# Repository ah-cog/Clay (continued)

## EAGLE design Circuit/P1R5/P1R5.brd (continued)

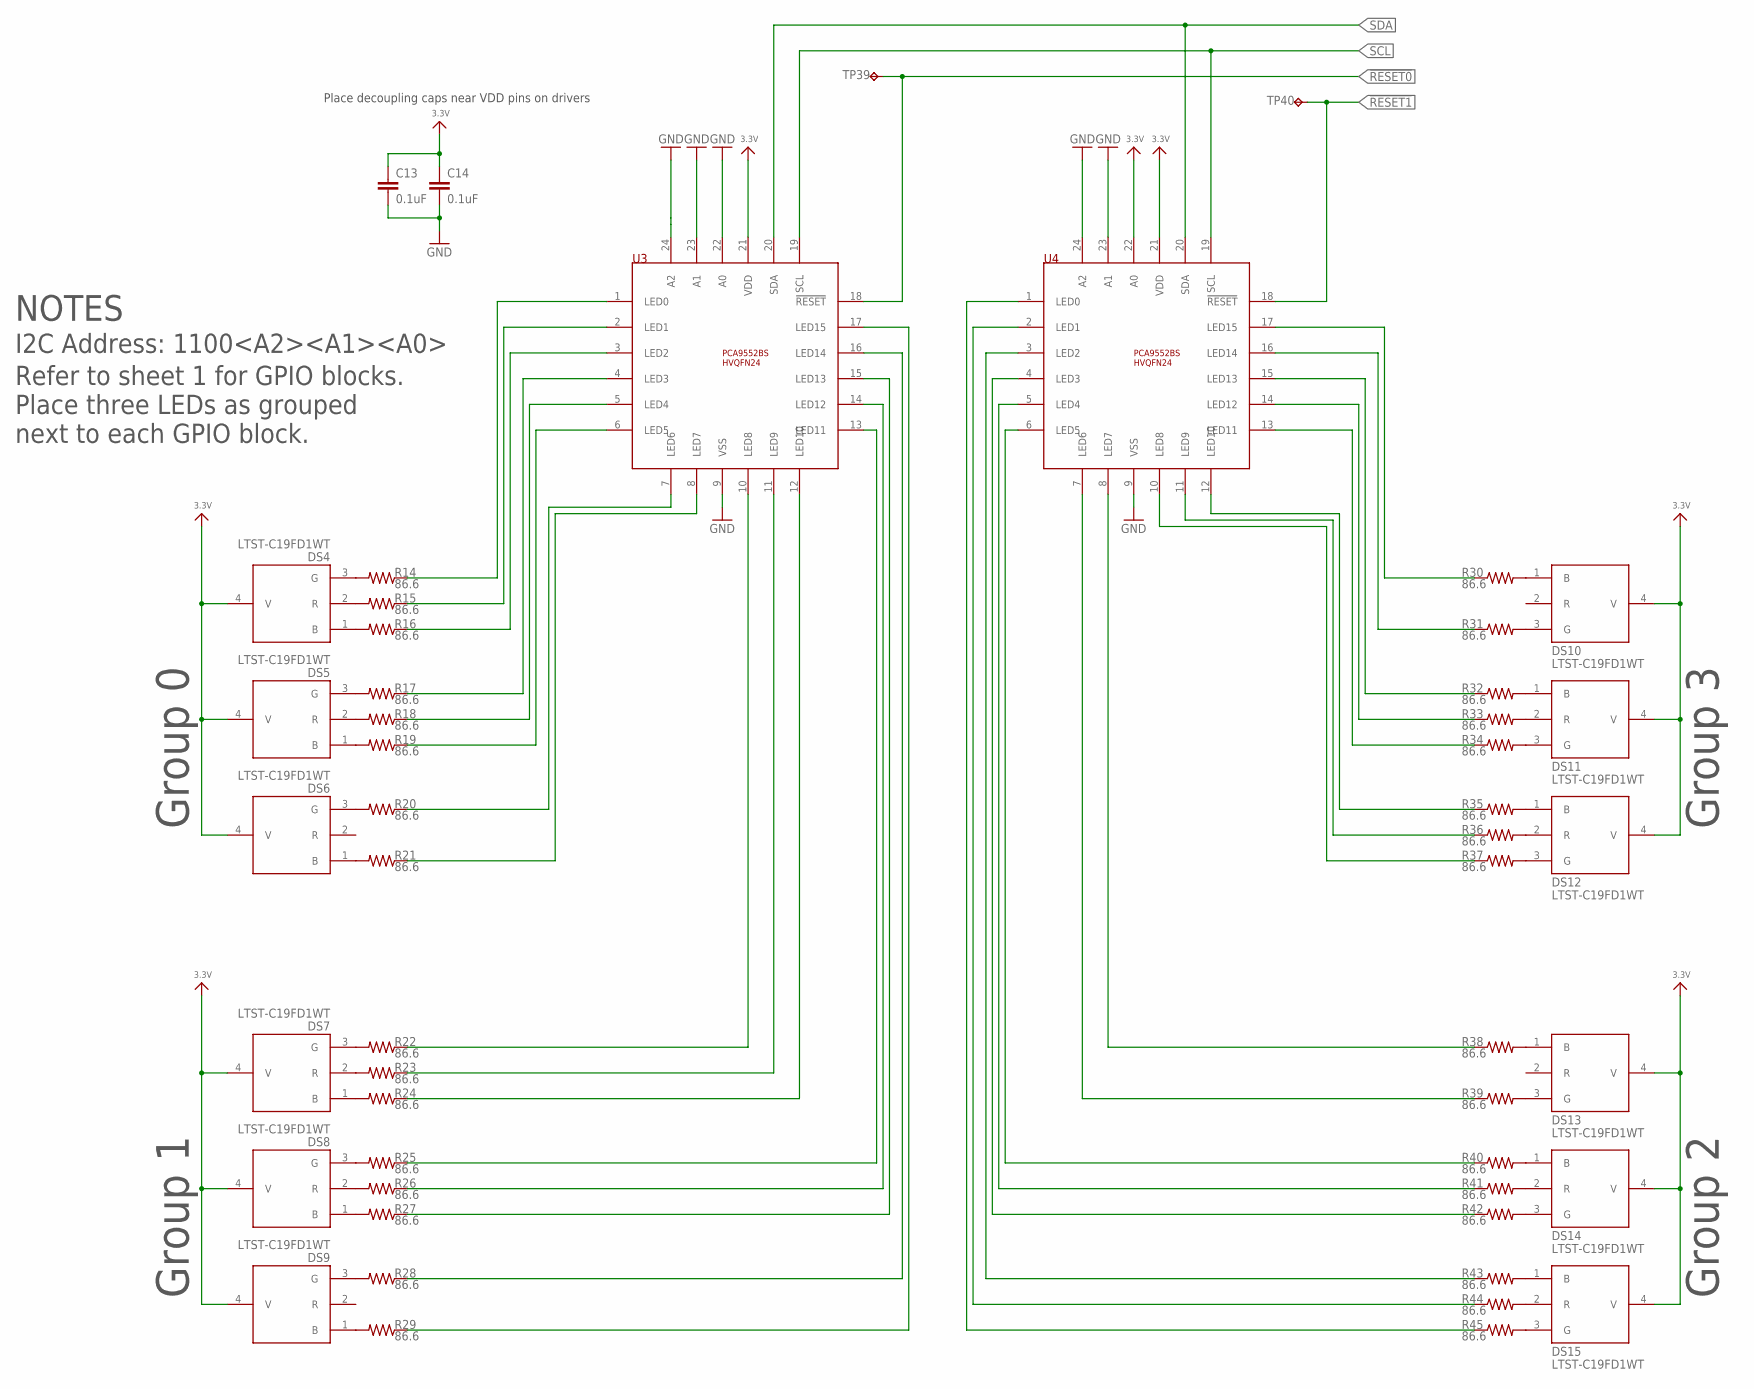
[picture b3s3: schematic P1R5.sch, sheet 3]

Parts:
C13, C14: 0.1uF; 0402-CAP; PARTNO C1005X7R1C104K050BC
DS4, DS5, DS6, DS7, DS8, DS9, DS10, DS11, DS12, DS13, DS14, DS15: LTST-C19FD1WT; PARTNO LTST-C19FD1WT
R14, R15, R16, R17, R18, R19, R20, R21, R22, R23, R24, R25, R26, R27, R28, R29, R30, R31, R32, R33, R34, R35, R36, R37, R38, R39, R40, R41, R42, R43, R44, R45: 86.6; _0402; PARTNO 5-1879213-0
TP39, TP40: TPTP08R; TP08R; PARTNO TEST POINT
U3, U4: PCA9552BS; HVQFN24; PARTNO PCA9552BS

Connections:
3.3V: C13.1, C14.1, DS4.4 (V), DS5.4 (V), DS6.4 (V), DS7.4 (V), DS8.4 (V), DS9.4 (V), DS10.4 (V), DS11.4 (V), DS12.4 (V), DS13.4 (V), DS14.4 (V), DS15.4 (V), U3.21 (VDD), U4.21 (VDD), U4.22 (A0); also elsewhere on the board
!RESET0: TP39.TP, U3.18 (!RESET); also elsewhere on the board
!RESET1: TP40.TP, U4.18 (!RESET); also elsewhere on the board
GND: C13.2, C14.2, U3.9 (VSS), U3.22 (A0), U3.23 (A1), U3.24 (A2), U4.9 (VSS), U4.23 (A1), U4.24 (A2); also elsewhere on the board
unnamed: DS8.2 (R), R26.2
unnamed: DS7.2 (R), R23.2
unnamed: DS7.1 (B), R24.2
unnamed: DS7.3 (G), R22.2
unnamed: DS8.1 (B), R27.2
unnamed: DS8.3 (G), R25.2
unnamed: DS10.3 (G), R31.2
unnamed: DS10.1 (B), R30.2
unnamed: DS9.1 (B), R29.2
unnamed: DS9.3 (G), R28.2
unnamed: R14.1, U3.1 (LED0)
unnamed: DS5.2 (R), R18.2
unnamed: R15.1, U3.2 (LED1)
unnamed: R16.1, U3.3 (LED2)
unnamed: DS14.1 (B), R40.2
unnamed: DS4.2 (R), R15.2
unnamed: DS11.2 (R), R33.2
unnamed: DS4.1 (B), R16.2
unnamed: DS4.3 (G), R14.2
unnamed: DS5.1 (B), R19.2
unnamed: DS5.3 (G), R17.2
unnamed: DS15.3 (G), R45.2
unnamed: DS12.1 (B), R35.2
unnamed: DS13.3 (G), R39.2
unnamed: R17.1, U3.4 (LED3)
unnamed: DS11.3 (G), R34.2
unnamed: DS14.3 (G), R42.2
unnamed: DS11.1 (B), R32.2
unnamed: DS12.3 (G), R37.2
unnamed: DS6.1 (B), R21.2
unnamed: DS6.3 (G), R20.2
unnamed: DS14.2 (R), R41.2
unnamed: DS13.1 (B), R38.2
unnamed: R18.1, U3.5 (LED4)
unnamed: DS15.1 (B), R43.2
unnamed: R19.1, U3.6 (LED5)
unnamed: R20.1, U3.7 (LED6)
unnamed: R21.1, U3.8 (LED7)
unnamed: R22.1, U3.10 (LED8)
unnamed: R23.1, U3.11 (LED9)
unnamed: R24.1, U3.12 (LED10)
unnamed: R25.1, U3.13 (LED11)
unnamed: R26.1, U3.14 (LED12)
unnamed: R27.1, U3.15 (LED13)
unnamed: R28.1, U3.16 (LED14)
unnamed: R29.1, U3.17 (LED15)
unnamed: DS12.2 (R), R36.2
unnamed: DS15.2 (R), R44.2
unnamed: R30.1, U4.17 (LED15)
unnamed: R31.1, U4.16 (LED14)
unnamed: R32.1, U4.15 (LED13)
unnamed: R33.1, U4.14 (LED12)
unnamed: R34.1, U4.13 (LED11)
unnamed: R35.1, U4.12 (LED10)
unnamed: R36.1, U4.11 (LED9)
unnamed: R37.1, U4.10 (LED8)
unnamed: R38.1, U4.8 (LED7)
unnamed: R39.1, U4.7 (LED6)
unnamed: R40.1, U4.6 (LED5)
unnamed: R41.1, U4.5 (LED4)
unnamed: R42.1, U4.4 (LED3)
unnamed: R43.1, U4.3 (LED2)
unnamed: R44.1, U4.2 (LED1)
unnamed: R45.1, U4.1 (LED0)
SCL: U3.19 (SCL), U4.19 (SCL); also elsewhere on the board
SDA: U3.20 (SDA), U4.20 (SDA); also elsewhere on the board

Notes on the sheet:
I2C Address: 1100<A2><A1><A0>
Place decoupling caps near VDD pins on drivers
Refer to sheet 1 for GPIO blocks. Place three LEDs as grouped next to each GPIO block.
NOTES
Group 0
Group 1
Group 2
Group 3

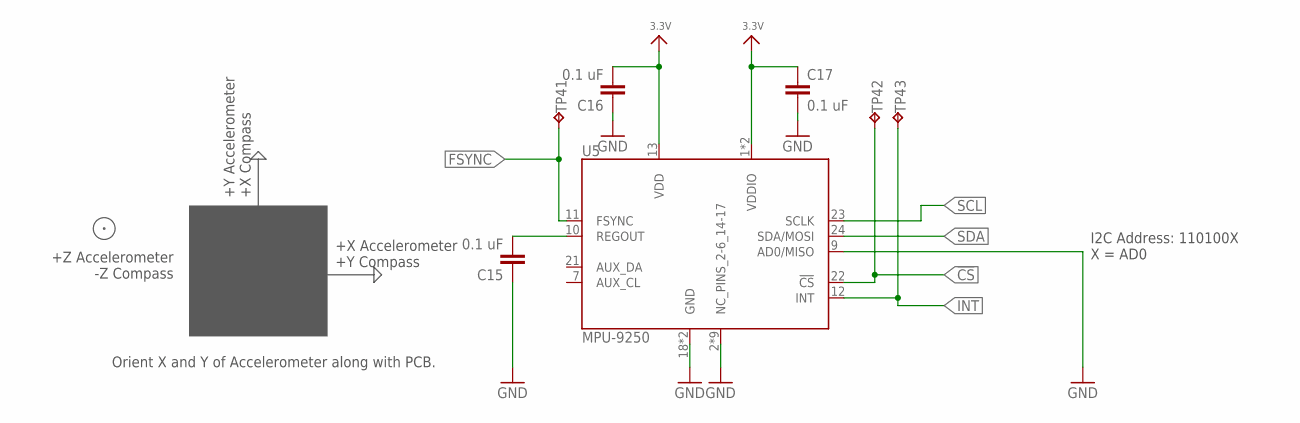
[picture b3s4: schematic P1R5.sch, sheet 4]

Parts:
C15, C16, C17: 0.1 uF; 0402-CAP; PARTNO C1005X7R1C104K050BC
TP41, TP42, TP43: TPTP08R; TP08R; PARTNO TEST POINT
U5: MPU-9250; QFN-24/3MM; PARTNO MPU-9250

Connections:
3.3V: C16.2, C17.1, U5.1 (VDDIO), U5.8 (VDDIO), U5.13 (VDD); also elsewhere on the board
!CS: TP42.TP, U5.22 (!CS); also elsewhere on the board
FSYNC: TP41.TP, U5.11 (FSYNC); also elsewhere on the board
GND: C15.1, C16.1, C17.2, U5.2 (NC_PINS_2-6_14-17), U5.3 (NC_PINS_2-6_14-17), U5.4 (NC_PINS_2-6_14-17), U5.5 (NC_PINS_2-6_14-17), U5.6 (NC_PINS_2-6_14-17), U5.9 (AD0/MISO), U5.14 (NC_PINS_2-6_14-17), U5.15 (NC_PINS_2-6_14-17), U5.16 (NC_PINS_2-6_14-17), U5.17 (NC_PINS_2-6_14-17), U5.18 (GND), U5.20 (GND); also elsewhere on the board
INT: TP43.TP, U5.12 (INT); also elsewhere on the board
unnamed: C15.2, U5.10 (REGOUT)
SCL: U5.23 (SCLK); also elsewhere on the board
SDA: U5.24 (SDA/MOSI); also elsewhere on the board

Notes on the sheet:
Orient X and Y of Accelerometer along with PCB.
+Y Accelerometer +X Compass
+X Accelerometer +Y Compass
I2C Address: 110100X X = AD0
+Z Accelerometer -Z Compass

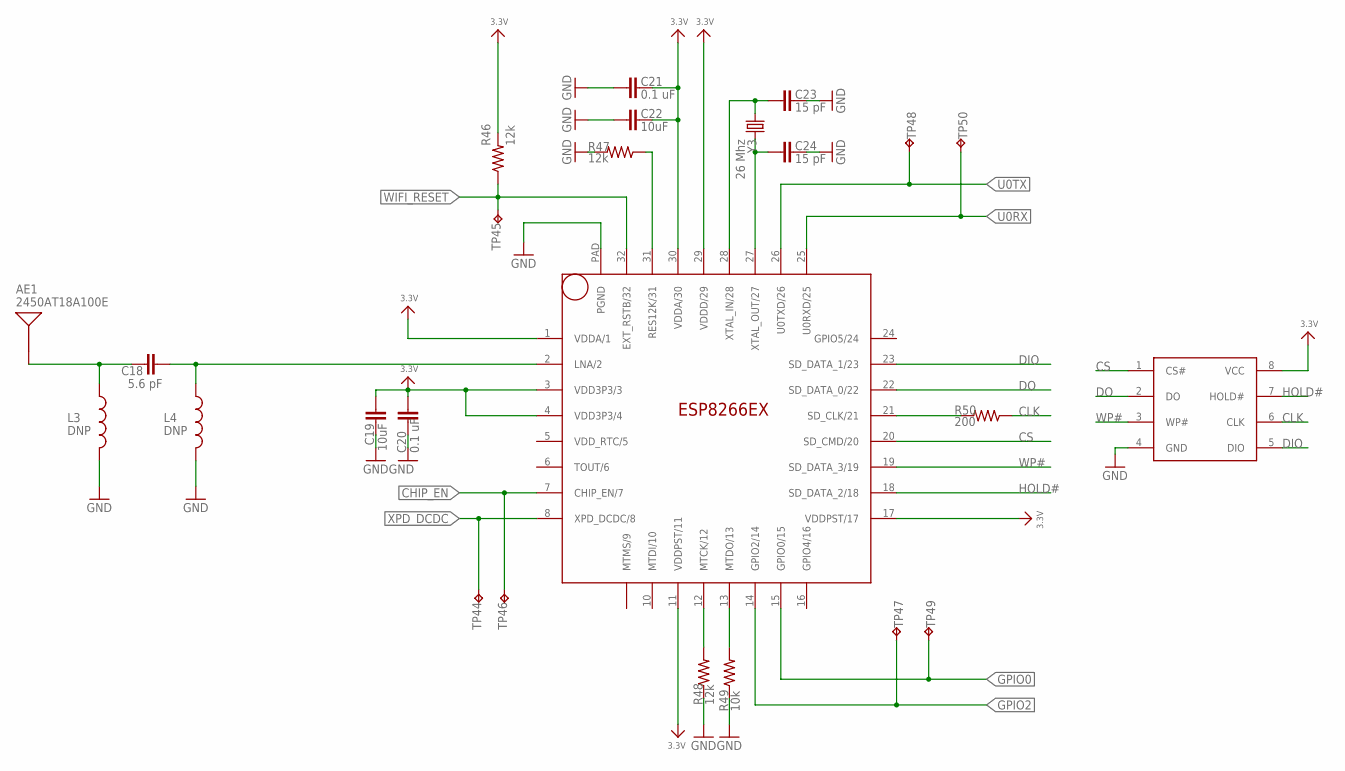
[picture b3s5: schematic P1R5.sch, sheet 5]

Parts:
AE1: 2450AT18A100E; ANTENNA-CHIP2; PARTNO 2450AT18A100E
C18: 5.6 pF; 0402-CAP; PARTNO GRM1555C1H5R6CA01D
C19, C22: 10uF; 0603-CAP; PARTNO C1608X7S0J106M080AC
C20, C21: 0.1 uF; 0402-CAP; PARTNO C1005X7R1C104K050BC
C23, C24: 15 pF; 0402-CAP; PARTNO C1005C0G1H150J050BA
L3, L4: DNP; 0603; PARTNO DNP
R46, R47, R48: 12k; _0402; PARTNO CRCW040212K0FKED
R49: 10k; _0402; PARTNO CRCW040210K0FKED
R50: 200; _0402; PARTNO CRCW0402200RFKED
TP44, TP45, TP46, TP47, TP48, TP49, TP50: TPTP08R; TP08R; PARTNO TEST POINT
U6: ESP8266EX; QFN32; PARTNO ESP8266EX
U7: 25Q40; SOP8; PARTNO 25Q40
Y3: 26 Mhz; CRYSTAL-SMD-5X3; PARTNO 7M-26.000MAAJ-T

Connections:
3.3V: C19.1, C20.2, C21.1, C22.1, R46.2, U6.1 (VDDA/1), U6.3 (VDD3P3/3), U6.4 (VDD3P3/4), U6.11 (VDDPST/11), U6.17 (VDDPST/17), U6.29 (VDDD/29), U6.30 (VDDA/30), U7.8 (VCC); also elsewhere on the board
CHIP_EN: TP46.TP, U6.7 (CHIP_EN/7); also elsewhere on the board
CLK: R50.1, U7.6 (CLK)
CS: U6.20 (SD_CMD/20), U7.1 (CS#)
DIO: U6.23 (SD_DATA_1/23), U7.5 (DIO)
DO: U6.22 (SD_DATA_0/22), U7.2 (DO)
GND: C19.2, C20.1, C21.2, C22.2, C23.2, C24.2, L3.2, L4.2, R47.2, R48.1, R49.1, U6.PAD (PGND), U7.4 (GND); also elsewhere on the board
GPIO0: TP49.TP, U6.15 (GPIO0/15); also elsewhere on the board
GPIO2: TP47.TP, U6.14 (GPIO2/14); also elsewhere on the board
HOLD#: U6.18 (SD_DATA_2/18), U7.7 (HOLD#)
unnamed: R50.2, U6.21 (SD_CLK/21)
unnamed: C18.2, L4.1, U6.2 (LNA/2)
unnamed: C24.1, U6.27 (XTAL_OUT/27), Y3.1
unnamed: C23.1, U6.28 (XTAL_IN/28), Y3.3 (2)
unnamed: AE1.FEED, C18.1, L3.1
unnamed: R48.2, U6.12 (MTCK/12)
unnamed: R49.2, U6.13 (MTDO/13)
unnamed: R47.1, U6.31 (RES12K/31)
U0RX: TP50.TP, U6.25 (U0RXD/25); also elsewhere on the board
U0TX: TP48.TP, U6.26 (U0TXD/26); also elsewhere on the board
WIFI_RESET: R46.1, TP45.TP, U6.32 (EXT_RSTB/32); also elsewhere on the board
WP#: U6.19 (SD_DATA_3/19), U7.3 (WP#)
XPD_DCDC: TP44.TP, U6.8 (XPD_DCDC/8); also elsewhere on the board

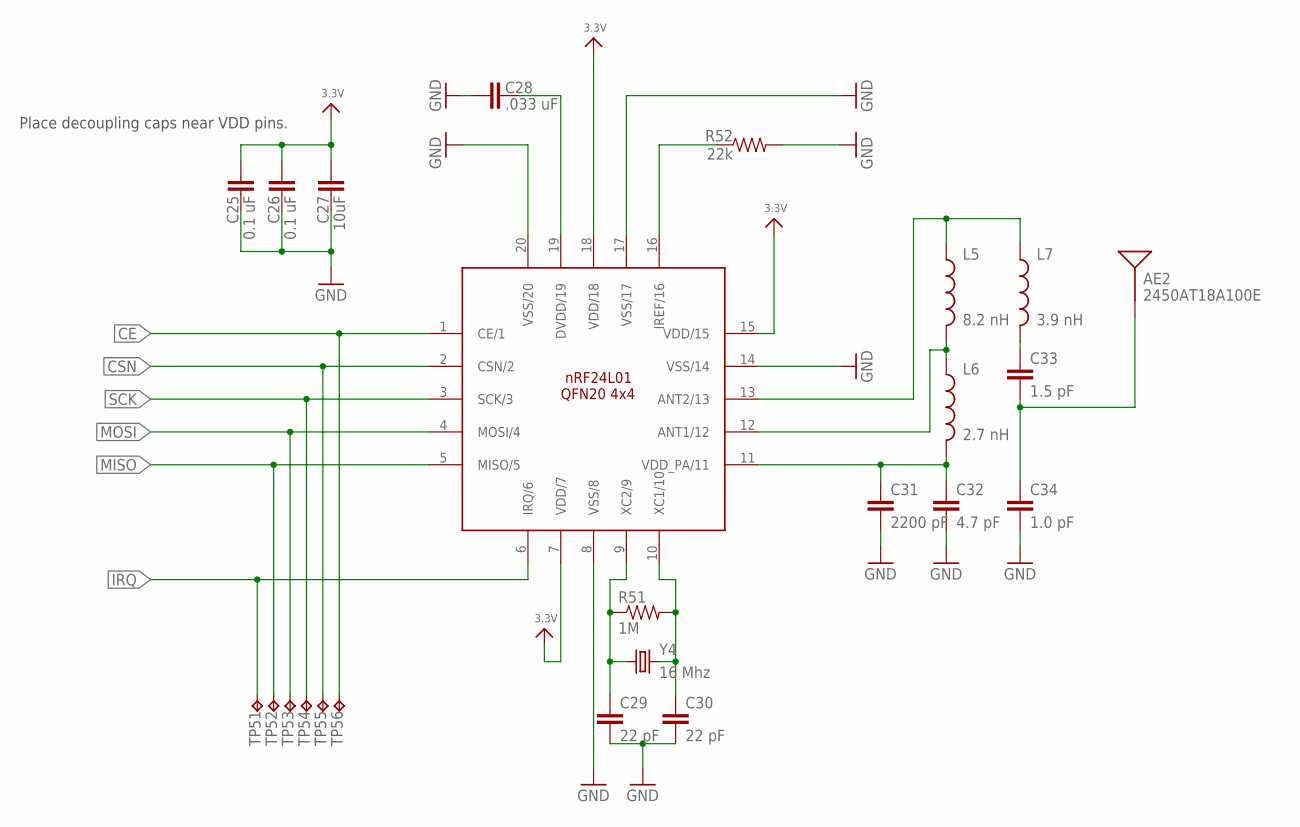
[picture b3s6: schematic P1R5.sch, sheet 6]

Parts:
AE2: 2450AT18A100E; ANTENNA-CHIP2; PARTNO 2450AT18A100E
C25, C26: 0.1 uF; 0402-CAP; PARTNO C1005X7R1C104K050BC
C27: 10uF; 0603-CAP; PARTNO C1608X7S0J106M080AC
C28: .033 uF; 0402-CAP; PARTNO C1005X7R1H333K050BB
C29, C30: 22 pF; 0402-CAP; PARTNO C1005C0G1H220J050BA
C31: 2200 pF; 0402-CAP; PARTNO C1005X7R1H222K050BA
C32: 4.7 pF; 0402-CAP; PARTNO CGA2B2C0G1H4R7C050BA
C33: 1.5 pF; 0402-CAP; PARTNO C1005C0G1H1R5B050BA
C34: 1.0 pF; 0402-CAP; PARTNO C1005C0G1H010B050BA
L5: 8.2 nH; C0402; PARTNO L-07C8N2JV6T
L6: 2.7 nH; C0402; PARTNO L-07C2N7SV6T
L7: 3.9 nH; C0402; PARTNO L-07C3N9SV6T
R51: 1M; _0402; PARTNO CRCW04021M00FKED
R52: 22k; _0402; PARTNO CRCW040222K0FKED
TP51, TP52, TP53, TP54, TP55, TP56: TPTP08R; TP08R; PARTNO TEST POINT
U8: NRF24L01; QFN20(4X4); PARTNO NRF24L01P-T
Y4: 16 Mhz; CRYSTAL-SMD-5X3; PARTNO 7B-16.000MAAJ-T

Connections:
3.3V: C25.1, C26.1, C27.1, U8.7 (VDD/7), U8.15 (VDD/15), U8.18 (VDD/18); also elsewhere on the board
CE: TP56.TP, U8.1 (CE/1); also elsewhere on the board
CSN: TP55.TP, U8.2 (CSN/2); also elsewhere on the board
GND: C25.2, C26.2, C27.2, C28.1, C29.2, C30.2, C31.2, C32.2, C34.2, R52.2, U8.8 (VSS/8), U8.14 (VSS/14), U8.17 (VSS/17), U8.20 (VSS/20); also elsewhere on the board
IRQ: TP51.TP, U8.6 (IRQ/6); also elsewhere on the board
MISO: TP52.TP, U8.5 (MISO/5); also elsewhere on the board
MOSI: TP53.TP, U8.4 (MOSI/4); also elsewhere on the board
unnamed: C29.1, R51.1, U8.9 (XC2/9), Y4.1
unnamed: C30.1, R51.2, U8.10 (XC1/10), Y4.3 (2)
unnamed: L5.1, L7.1, U8.13 (ANT2/13)
unnamed: R52.1, U8.16 (IREF/16)
unnamed: C28.2, U8.19 (DVDD/19)
unnamed: L5.2, L6.1, U8.12 (ANT1/12)
unnamed: AE2.FEED, C33.2, C34.1
unnamed: C33.1, L7.2
unnamed: C31.1, C32.1, L6.2, U8.11 (VDD_PA/11)
SCK: TP54.TP, U8.3 (SCK/3); also elsewhere on the board

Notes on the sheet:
Place decoupling caps near VDD pins.

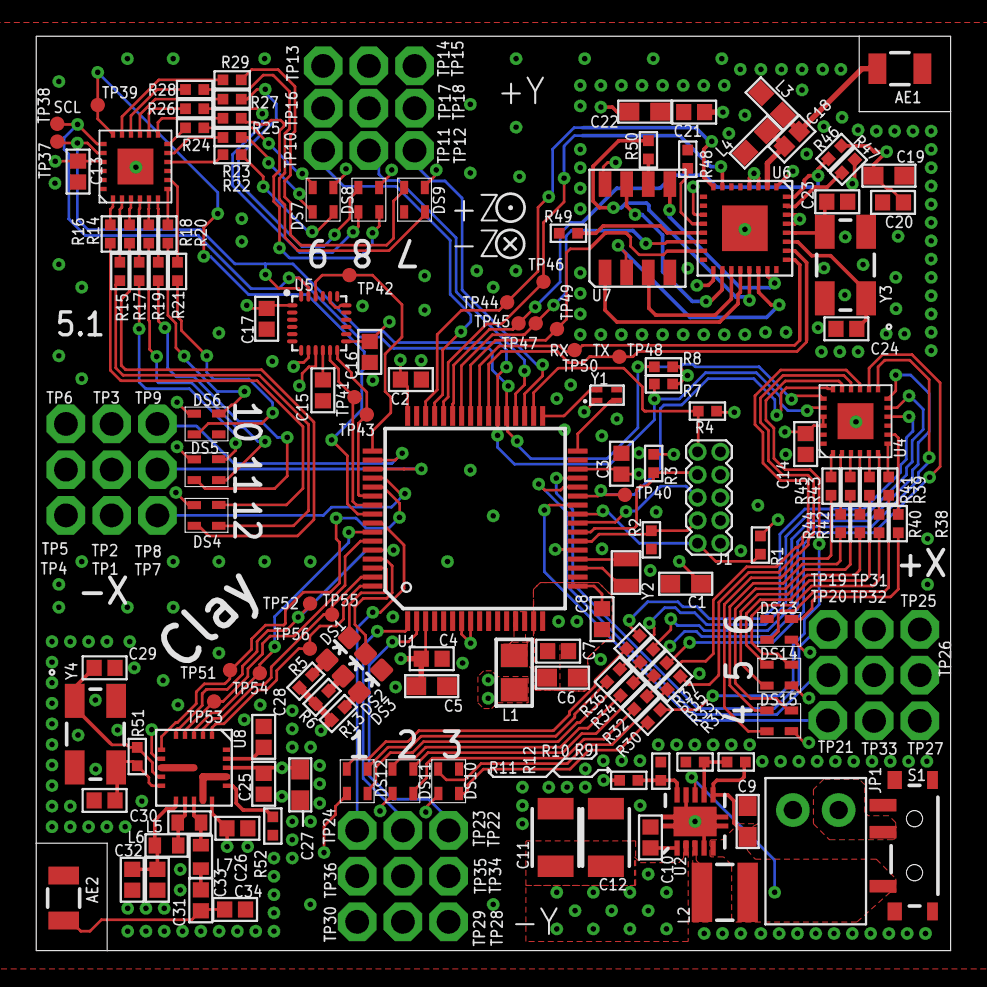
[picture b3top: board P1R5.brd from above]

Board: 4 copper layers, 50.8 x 50.8 mm, 182 parts (0 on the bottom side), 144 nets.

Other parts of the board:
DRILEGEND: DRILEGEND

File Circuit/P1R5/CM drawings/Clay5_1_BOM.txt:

Qty-1	Part References	Value	Package	Mfg Part Num	Mfg Name	VID	Vendor Part Num	Description	Pkg Code	XREF
1	C28	.033 uF	0402-CAP	C1005X7R1H333K050BB	TDK Corporation	DK	445-7334-1-ND	CAP CER 0.033UF 50V 10% X7R 0402	402	REF169
15	"C15, C16, C17, C20, C21, C25, C26, C2, C3, C4, C7, C8, C10, C13, C14"	0.1uF	0402-CAP	C1005X7R1C104K050BC	TDK Corporation	DK	445-4952-1-ND	CAP CER 0.1UF 16V 10% X7R 0402	402	REF167
1	C34	1.0 pF	0402-CAP	C1005C0G1H010B050BA	TDK Corporation	DK	445-4854-1-ND	CAP CER 1PF 50V C0G 0402	402	REF174
1	R11	1.2M	_0402	CRCW04021M20FKED	Vishay Dale	DK	541-1.20MLCT-ND	RES SMD 1.2M OHM 1% 1/16W 0402	402	REF184
1	C33	1.5 pF	0402-CAP	C1005C0G1H1R5B050BA	TDK Corporation	DK	445-4858-1-ND	CAP CER 1.5PF 50V C0G 0402	402	REF170
1	R51	1M	_0402	CRCW04021M00FKED	Vishay Dale	DK	541-1.00MLCT-ND	RES SMD 1M OHM 1% 1/16W 0402	402	REF182
1	L2	"2.2UH, 2.1A"	LPS3015	BRL3225T2R2M	Taiyo Yuden	DK	587-2165-1-ND	FIXED IND 2.2UH 1.6A 78 MOHM SMD	1210	REF141
1	L6	2.7 nH	C0402	L-07C2N7SV6T	Johanson Technology Inc	DK	712-1415-1-ND	FIXED IND 2.7NH 300MA 170 MOHM	402	REF140
1	R9	2M	_0402	CRCW04022M00FKED	Vishay Dale	DK	541-2.00MLCT-ND	RES SMD 2M OHM 1% 1/16W 0402	402	REF183
1	J1	"2X5_0.05""_CORTEX_DEBUGTH_NOKEY_UNSHROUDED"	"2X5_0.05""_TH_NS"	20021111-00010T4LF	FCI	DK	609-3712-ND	CONN HEADER 10POS UNSHD VERT T/H	*	REF156
1	L7	3.9 nH	C0402	L-07C3N9SV6T	Johanson Technology Inc	DK	712-1459-1-ND	FIXED IND 3.9NH 300MA 220 MOHM	402	REF137
1	C32	4.7 pF	0402-CAP	CGA2B2C0G1H4R7C050BA	TDK Corporation	DK	445-5577-1-ND	CAP CER 4.7PF 50V C0G 0402	402	REF175
1	C18	5.6 pF	0402-CAP	GRM1555C1H5R6CA01D	Murata Electronics North America	DK	490-6250-1-ND	CAP CER 5.6PF 50V NP0 0402	402	REF176
1	L5	8.2 nH	C0402	L-07C8N2JV6T	Johanson Technology Inc	DK	712-1420-1-ND	FIXED IND 8.2NH 250MA 400 MOHM	402	REF143
1	Y1	8MHz	ASCO	ASCO-8.000MHZ-EK-T3	Abracon LLC	DK	535-12077-1-ND	OSC XO 8.000MHZ CMOS SMD	4-SMD	REF165
7	"R1, R2, R3, R4, R7, R8, R49"	10k	_0402	CRCW040210K0FKED	Vishay Dale	DK	541-10.0KLCT-ND	RES SMD 10K OHM 1% 1/16W 0402	402	REF180
7	"C1, C5, C6, C9, C19, C22, C27"	10uF	0603-CAP	C1608X7S0J106M080AC	TDK Corporation	DK	445-9104-1-ND	CAP CER 10UF 6.3V 20% X7S 0603	603	REF166
3	"R46, R47, R48"	12k	_0402	CRCW040212K0FKED	Vishay Dale	DK	541-12.0KLCT-ND	RES SMD 12K OHM 1% 1/16W 0402	402	REF178
2	"C23, C24"	15 pF	0402-CAP	C1005C0G1H150J050BA	TDK Corporation	DK	445-1237-1-ND	CAP CER 15PF 50V 5% C0G 0402	402	REF171
1	Y4	16 Mhz	CRYSTAL-SMD-5X3	7B-16.000MAAJ-T	TXC CORPORATION	DK	887-1104-1-ND	"Crystal 16.0000MHz 30ppm 18pF 40 Ohm -20°C - 70°C Surface Mount 4-SMD, No Lead (DFN, LCC)"	SMD4	REF144
2	"C29, C30"	22 pF	0402-CAP	C1005C0G1H220J050BA	TDK Corporation	DK	445-1239-1-ND	CAP CER 22PF 50V 5% C0G 0402	402	REF173
1	R52	22k	_0402	CRCW040222K0FKED	Vishay Dale	DK	541-22.0KLCT-ND	RES SMD 22K OHM 1% 1/16W 0402	402	REF181
2	"C11, C12"	22uF	1210	C3225X7R1A226K230AC	TDK Corporation	DK	445-6863-1-ND	CAP CER 22UF 10V 10% X7R 1210	1210	REF168
3	"R5, R6, R13"	25	_0402	CRCW040224R9FKED	Vishay Dale	DK	541-24.9LCT-ND	RES SMD 24.9 OHM 1% 1/16W 0402	402	REF187
1	U7	25Q40	SOP8	25Q40	WinBond Electronics	DK	W25Q40BWSNIG-ND	IC FLASH 4MBIT 80MHZ 8SOIC	SOIC-8	REF162
1	Y3	26 Mhz	CRYSTAL-SMD-5X3	7M-26.000MAAJ-T	TXC CORPORATION	DK	887-1133-1-ND	"Crystal 26.0000MHz 30ppm 18pF 60 Ohm -20°C - 70°C Surface Mount 4-SMD, No Lead (DFN, LCC)"	SMD4	REF146
1	Y2	34.728kHz	ABS06	ABS06-32.768KHZ-T	Abracon LLC	DK	535-10104-1-ND	Crystal 32.7680kHz 20ppm 12.5pF 90 kOhm -40°C - 85°C Surface Mount 2-SMD	2-SMD	REF164
32	"R14, R15, R16, R17, R18, R19, R20, R21, R22, R23, R24, R25, R26, R27, R28, R29, R30, R31, R32, R33, R34, R35, R36, R37, R38, R39, R40, R41, R42, R43, R44, R45"	86.6	_0402	5-1879213-0	TE Connectivity AMP Connectors	DK	A103000CT-ND        	RES SMD 86.6 OHM 0.1% 1/16W 0402	402	REF177
1	R50	200	_0402	CRCW0402200RFKED	Vishay Dale	DK	541-200LCT-ND	RES SMD 200 OHM 1% 1/16W 0402	402	REF179
2	"R10, R12"	220K	_0402	CRCW0402220KFKED	Vishay Dale	DK	541-220KLCT-ND	RES SMD 220K OHM 1% 1/16W 0402	402	REF186
1	L1	600 OHM/100 MHZ	805	BK2125HM601-T	Taiyo Yuden	DK	587-1902-1-ND	FERRITE BEAD 600 OHM 0805	805	REF142
1	C31	2200 pF	0402-CAP	C1005X7R1H222K050BA	TDK Corporation	DK	445-1257-1-ND	CAP CER 2200PF 50V 10% X7R 0402	402	REF172
2	"AE1, AE2"	2450AT18A100E	ANTENNA-CHIP2	2450AT18A100E	Johanson Technology Inc	DK	712-1005-1-ND	ANTENNA CHIP 2.4GHZ	*	REF147
1	S1	CUS-12TB	SWITCH-SPST-SMD-A	CUS-12TB	Copal Electronics Inc	DK	563-1102-1-ND	SWITCH SLIDE SPDT 300MA 4V	*	REF153
2	"L3, L4"	DNP	603	DNP	DO NOT PLACE	(N/A)	DO NOT PLACE	DO NOT PLACE	*	REF14
1	U6	ESP8266EX	QFN32	ESP8266EX	Expressif	AB	ESP8266EX	B/G/N Wi-Fi	QFN32_5x5mm	REF163
12	"DS4, DS5, DS6, DS7, DS8, DS9, DS10, DS11, DS12, DS13, DS14, DS15"	LTST-C19FD1WT	LTST-C19FD1WT	LTST-C19FD1WT	Lite-On Inc	DK	160-2022-1-ND	LED RGB 605/525/470NM DIFF SMD	SMD4	REF151
3	"DS1, DS2, DS3"	LTST-C191TBKT	LED-0603	LTST-C191TBKT	Lite-On Inc	DK	160-1647-1-ND	LED 468NM BLUE CLEAR 0603 SMD	603	REF152
1	JP1	M20PTH	JST_2PIN	S2B-PH-K-S(LF)(SN)	JST	DK	455-1719-ND	2-pin JST	M20PTH	REF159
1	U1	MK20DX256VLH7	MK20DX256VLH7	MK20DX256VLH7	Freescale	DK	MK20DX256VLH7-ND	IC MCU ARM 256KB FLASH 64LQFP	LQFP64	REF95
1	U5	MPU-9250	QFN-24/3MM	MPU-9250	InvenSense	DK	1428-1019-1-ND	GYRO/ACCEL/COMPASS/9-AXIS	QFN24_3x3mm	REF161
1	U8	NRF24L01	QFN20(4X4)	NRF24L01P-T	Nordic Semiconductor	DK	1490-1019-ND	IC RF TRANSCEIVER 2.4GHZ 20QFN	QFN20	REF96
2	"U3, U4"	PCA9552BS	HVQFN24	PCA9552BS	NXP Semiconductors	DK	568-3389-1-ND	IC LED Driver Linear I2C Dimming 25mA 24-HVQFN (4x4)	HVQFN24	REF158
36	"TP1, TP2, TP3, TP4, TP5, TP6, TP7, TP8, TP9, TP10, TP11, TP12, TP13, TP14, TP15, TP16, TP17, TP18, TP19, TP20, TP21, TP22, TP23, TP24, TP25, TP26, TP27, TP28, TP29, TP30, TP31, TP32, TP33, TP34, TP35, TP36"	TPPAD1-13	P1-13	TEST POINT	TEST POINT	(N/A)	TEST POINT	TEST POINT	*	REF160
1	U2	TPS61200	QFN-10_PAD	TPS61200DRCR	Texas Instruments	DK	296-27017-1-ND	IC REG BOOST ADJ 1.2A SYNC 10SON	SON10	REF98
20	"TP37, TP38, TP39, TP40, TP41, TP42, TP43, TP44, TP45, TP46, TP47, TP48, TP49, TP50, TP51, TP52, TP53, TP54, TP55, TP56"	TPTP08R	TP08R	TEST POINT	TEST POINT	(N/A)	TEST POINT	TEST POINT	*	REF160

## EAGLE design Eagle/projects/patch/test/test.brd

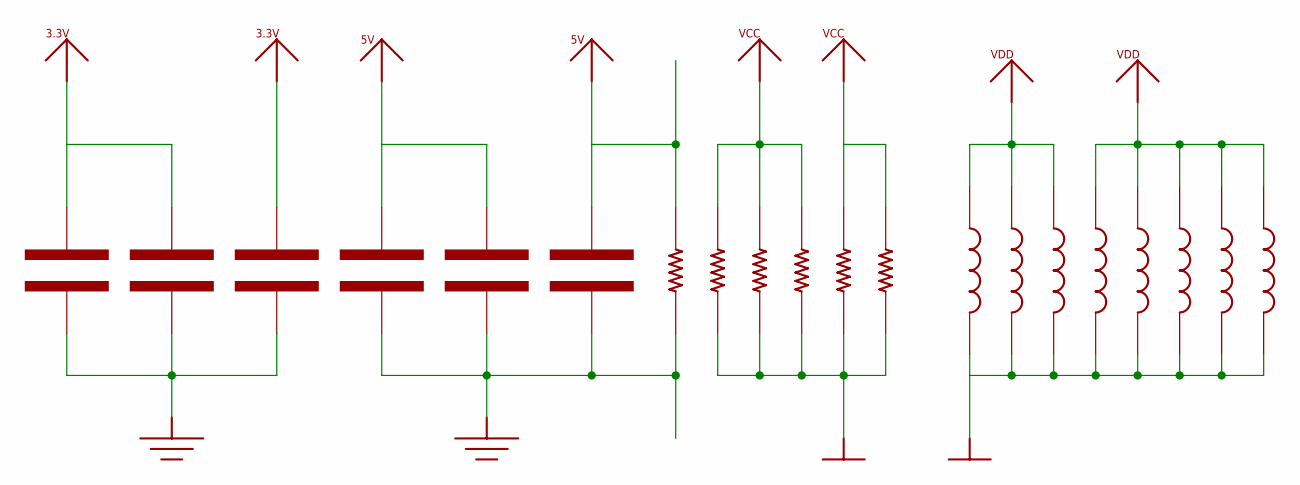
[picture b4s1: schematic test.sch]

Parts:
C1, C2: CAP-0402; 0402-CAP
C3, C4: CAP-0603; 0603-CAP
C5, C6: CAP-0805; 0805
L1, L2: IND-0402; 0402-CAP
L3, L4: IND-0603; 0603-CAP
L5, L6: IND-0805; 0805
L7, L8: IND-1206; 1206
R1, R2: RES-0402; 0402-RES
R3, R4: RES-0603; 0603-RES
R5, R6: RES-0805; 0805

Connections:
3.3V: C1.1, C2.1, C3.1
5V: C4.1, C5.1, C6.1, R1.1
GND: C1.2, C2.2, C3.2, C4.2, C5.2, C6.2, R1.2
VCC: R2.1, R3.1, R4.1, R5.1, R6.1
VDD: L1.1, L2.1, L3.1, L4.1, L5.1, L6.1, L7.1, L8.1
VSS: L1.2, L2.2, L3.2, L4.2, L5.2, L6.2, L7.2, L8.2, R2.2, R3.2, R4.2, R5.2, R6.2

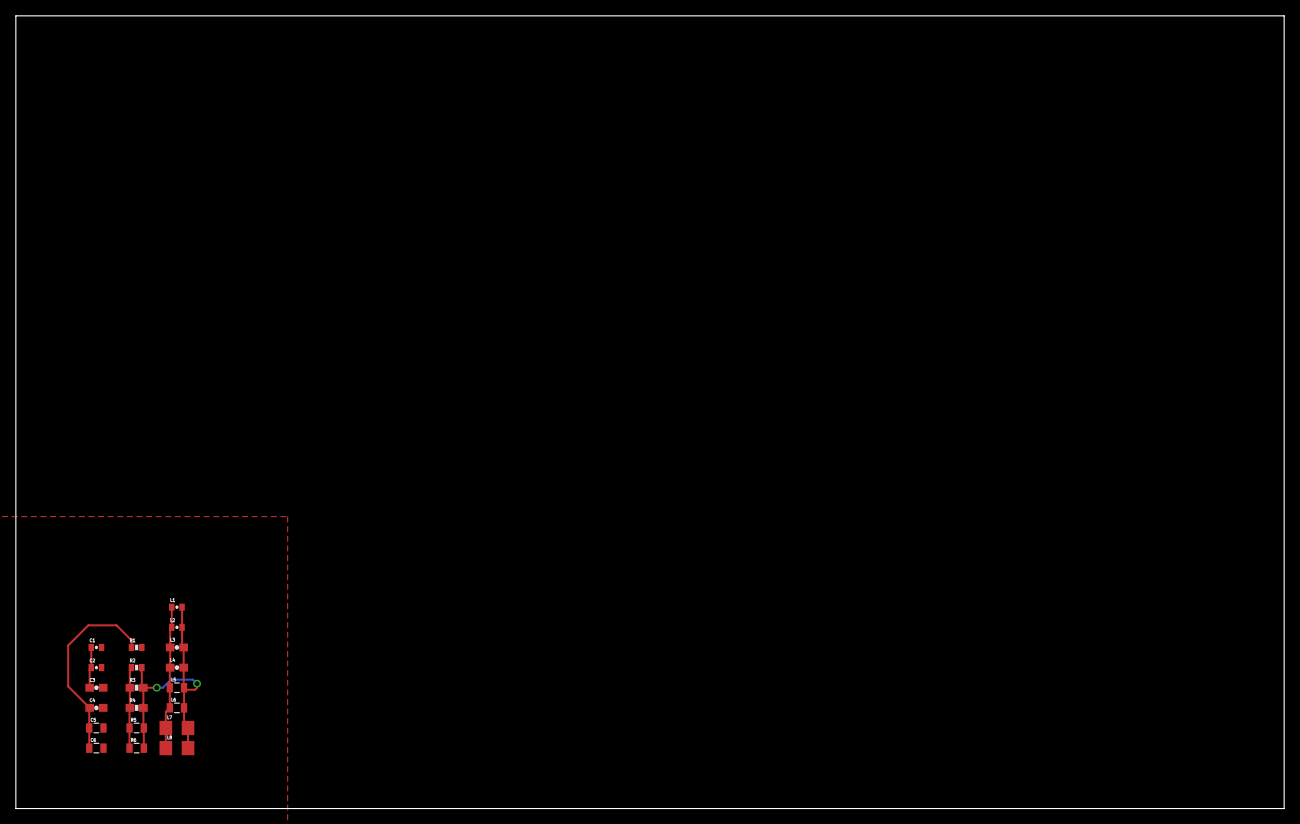
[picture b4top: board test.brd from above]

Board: 2 copper layers, 160.0 x 100.0 mm, 20 parts (0 on the bottom side), 6 nets.

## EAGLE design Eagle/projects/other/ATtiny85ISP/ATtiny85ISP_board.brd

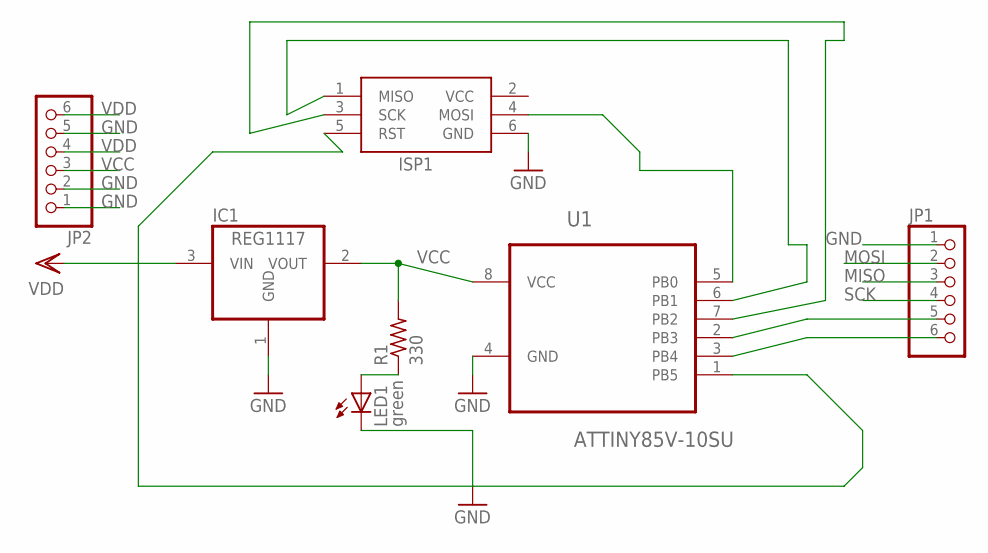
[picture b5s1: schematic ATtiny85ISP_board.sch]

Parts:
IC1: REG1117; SOT223
ISP1: AVRISP-6; AVRISP
JP1, JP2: PINHD-1X6; 1X06
LED1: green; CHIPLED_0805
R1: 330; M1206
U1: ATTINY85V-10SU; SOIC127P798X216-8N

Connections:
GND: IC1.1 (GND), ISP1.6 (GND), JP1.1, JP2.1, JP2.2, JP2.5, LED1.C, U1.4 (GND)
MISO: ISP1.1 (MISO), JP1.3, U1.6 (PB1)
MOSI: ISP1.4 (MOSI), JP1.2, U1.5 (PB0)
unnamed: LED1.A, R1.1
PIN3: JP1.5, U1.2 (PB3)
PIN4: JP1.6, U1.3 (PB4)
RST: ISP1.5 (RST), U1.1 (PB5)
SCK: ISP1.3 (SCK), JP1.4, U1.7 (PB2)
VCC: IC1.2 (VOUT), ISP1.2 (VCC), JP2.3, R1.2, U1.8 (VCC)
VDD: IC1.3 (VIN), JP2.4, JP2.6

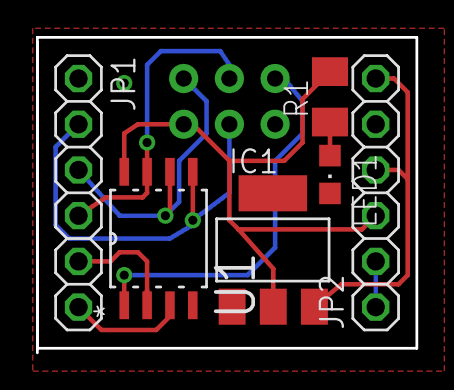
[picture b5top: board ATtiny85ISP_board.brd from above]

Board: 2 copper layers, 21.1 x 17.3 mm, 7 parts (1 on the bottom side), 10 nets.

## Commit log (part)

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2015-07-20 Gerbers for R3 and R4
2015-07-25 Created iffy Eagle library. Includes functional resistors, capacitors, inductors for sizes 0402, 0603, 0805 and 1206, along with supply symbols
2015-08-03 Added R5 with ground and power planes. No rerouting done yet
2015-08-03 hierarchical blocks done.
2015-08-04 Changed name of Wi-Fi web server added in previous commit.
2015-08-05 moved libraries, regenerated PCB, reannotated design, connected hierarchical blocks.
2015-08-07 Mas cleanup
2015-08-08 More cleanup.
2015-08-09 Matched all parts to bom-ex db.
2015-08-09 Added HTTP POST request body content parser.
2015-08-10 Got majority of PCB layout done.
2015-08-13 Everything but 3 banks of LED's is routed.
2015-08-14 Finished routing PCB. Put on some labels.
    DOPE
2015-08-17 Gerbers generated
2015-08-17 Updated the R5 Gerber .zip.
2015-08-18 Added basic interactive "REPL" pattern.
2015-08-21 Added a firmware demo that bridges across serial devices. This allows, for example, a terminal running on the MK20 to provide direct access another serial device (e.g., ESP8266).
2015-08-28 Added clay_demo_i2c to Clay Revision 4.
2015-08-31 Created working demo projects for ESP8266 and MPU9250 peripherals. Added non-working demo for nRF24L01+ (work in progress).
2015-08-31 Refactored clay_demo_esp8266 with a better driver design pattern.
2015-09-01 Removed files specific to Pixel. Pixel files will be moved to a different repository.
2015-09-04 added indexes to tplace on crystals
2015-09-05 added jflash project for MK20DX256VLH7
2015-09-09 Finished basic ESP8266 device driver and web server based on polling.
2015-09-11 Added port numbers to schematic.
2015-09-12 Got RGB LEDs working. Current code can only set the output on the driver at the address set in PE, and it turns on all of the LEDs.
2015-09-15 added GPIOs for IMU, started stubbing in some code for the driver.
2015-09-16 Removed RingBufferUInt8 from ESP8266 driver for Clay 5.
2015-09-16 Integrated barebones I/O channel (i.e., GPIO) controller support into Clay 5 firmware.
2015-09-18 More work on IMU. Got accel and gyro reading, not yet reading data from the compass, but it appears to be a configuration issue.
2015-09-25 Fixed fab drawing
2015-09-27 Added register map for MPU9250, got magnetometer working and updated code for z-axis accelerometer
2015-10-04 Added mesh 'baremetal' demo without RTOS. Works consistently on startup, then consistently stops working after a few successful receptions.
2015-10-04 got NRF working reliably. Now ignoring the packet loss counter.
2015-10-05 Added incoming message queue.
2015-11-04 Added RadioHead source for NRF24.
    Still need to add SPI driver for MK20
2015-11-19 mesh working both directions. each board will send once and then switch to receiving.
    Currently only works with two boards. define MESH_ITEM_1 in main.cpp for
    one board, comment it out for the other board. when powered up at the
    same time, one board will send, the other will receive. a board will
    receive until it has successfully recovered a message, then send once.
    It is easy to imagine a situation where this just stops working, the
    receiving node simply needs to drop a message. still, it's reliably
2015-11-26 added pwm output mode for IMU data.
2015-12-01 Added support for automatically collecting data at different message periods.
2015-12-03 Added HTTP POST request. Added UDP server, sending, and broadcast.
2015-12-03 updated limits in mesh_statistics.c
2015-12-05 got imu driver to program successfully. Interrupts not yet firing.
2015-12-07 added dmp_imu to set up the IMU using the invensense driver and keep a ring buffer of the last 100 measurements.
2015-12-09 added cis database and a couple of datasheets
2015-12-12 All parts added, first pass at schematic complete.
2015-12-13 First pass at layout complete.
2015-12-14 added renamed gerbers for smartproto
2015-12-16 added more price quotes from vendors. R6_bom_dk_ab_mous has the prices we got for everything.
2015-12-19 updated flash library with methods for writing byte, word, dword. added copy from and copy to methods, and multi-byte read start/stop method
2015-12-21 added flash libraries to bootloader_firmware project, and resized the memory available for that project binary.
2015-12-22 Updated ESP8266 driver for bootloader.
2015-12-22 Integrated firmware downloading and flash writing functionality. Untested.
2015-12-22 Added mesh library
2015-12-23 Updated ESP8266 driver and integration for downloading firmware. First commit with fully functional download. Still untested.
2015-12-27 Added loop reset when all behaviors are removed from the loop.
2016-01-07 Ported Invensense IMU driver into CPP project.
2016-01-10 Updated memory locations and hacked up some firmware update logic.
2016-01-12 Revert "Success! Bootloader downloads test firmware and runs it!"
    This reverts commit 7866e8420944d9d13b5cf2a81f84b819ecc6c24b.
2016-01-14 Added working implementation of CRC16 checksum.
2016-01-19 Completed initial bootloader implementation. Tested, but there might be some edge cases.
2016-01-21 Updated priorities for timer, mesh IRQ, and mesh SPI in CPP project.
2016-01-23 Dropped unused debug and build configurations from projects I'm still using. standardized debug config names.
2016-01-24 Bidirectional kinda working between 3 modules while everything else runs in background.
2016-01-27 Added bringup project for C6, got tick working, started on RGB driver.
2016-01-28 Updated gerber package.
2016-02-07 Updated references to be relative to main orcad project. Added my capture.ini.
2016-02-08 hopefully undoing changes from last commit.
2016-02-14 remade c6r2 gerbers. added renaming batch, got LED driver and demo working.
2016-02-19 Got it going, kinda. Only 9 chars round-trip though.
2016-02-25 Renamed directory for ESP8266EX_Firmware project
2016-02-29 Back to basics: got 4 tasks running on ESP doing dumbed-down versions of udp tx, rx, and serial tx,rx
2016-03-03 Started working on TCP receive side. Not yet working.
2016-03-08 Moved from status to dynamic message allocation for UDP communications over Wi-Fi.
2016-03-12 Updated firmware.
2016-03-12 Got UDP working with new serialization.
2016-03-13 UDP and TCP work. TCP does bidirectional communications now.
2016-03-16 ADC works. Button working well. BOM and Schematic change
    Button works better with 10k pull up and 100k in series with UVLO
    blocking diode. The schematic and BOM have been updated.
    There's code (in Application.c for now) that monitors VBat line and
    turns the micro off when the voltage drops below 3.2v.
    There's code for the soft power-off in application.c too.
2016-03-20 Refactored Clay.
2016-03-21 UDP communications.
2016-03-22 Fixed bug in message format.
2016-03-22 removed some debug prints from ESP firmware and comment out wifi test in k64/main.
2016-03-25 Added destination address to serialized message string.
2016-03-27 updated serialized message format. added commands for get IP, get gateway ip, get subnet mask
2016-03-27 Using UUIDs rather than tags.
2016-03-28 updated processorExpert components for GPIOs and updated driver to match
2016-03-29 Renamed Messenger to Message.
2016-03-29 removed unnecessary socket closure.
2016-03-30 Started implementing button interaction.
2016-03-30 Added buzzer and message actions.
2016-03-31 missed these in last commit somehow.
2016-04-02 Implemented all actions.
2016-04-04 Updated GPIO class. Ports 4 and 6 are now ADC and PWM respectively.
2016-04-05 TCP tx/rx, udp tx, and ip message working with application loop.
2016-04-06 added an identifier string to command responses for getting IP, gateway, subnet. Implemented the get connection status function.
2016-04-06 Fixed messaging bug.
2016-04-08 Implemented priority manager on ESP8266.
2016-04-09 implemented ring buffer for TCP RX. added debug messages to priority check. changed thresholds. added echo to application.c for testing.
2016-04-13 Reduced memory usage on ESP and everything got a lot more stable. Updated priority manager to run in its own task.
2016-04-16 fixed another major bug in the TCP RX queue. The swap operation was not allocating enough memory.
    We were also using strcpy on things that weren't guaranteed to be null
    terminated in the swap.
2016-04-16 inadvertent checkin last time, deleted more than intended
2016-04-17 Missed some updated references in my last commit.
2016-04-18 added demo for IR Range finder. Added periodic method to check GPIOs and update channel_profile.
2016-04-22 removed voltage calibration from GPIO. Updated the calibration in voltage controlled servo demo to work from ADC counts.
2016-04-23 Added trigger.
2016-04-23 Teseted trigger.
2016-04-24 Added support for signal messages to set pwm output. Implemented the hardware interface struct with the functions available per channel
2016-04-24 Added null checking to deinit's in GPIO. De-init on null device data pointer causes crash. Removed exit and printf from Hex_String_To_UInt
    Found parsing error in Get_Token_With_Delimiter.
    Updated Perform_Signal_Action to treat the incoming period as a value in
    microseconds.
2016-04-25 Fixed pause bug in event.
2016-04-27 Got Wifi initialization working in bootloader.
2016-04-29 Implemented HTTP message type on outgoing side of TCP. Am able to get responses back from webserver, but they are sent to the uC line by lin
2016-05-01 Found bug in multibyte ring buffer. Finished implementing multibyte_ring_buffer in tcp_combined. Implemented HTTP message parsing on ESP.
2016-05-02 Fixed minor bug in HTTP receive on ESP that was returning extra bytes. Got information fields writable/readable in firmware.
2016-05-03 Implemented method to parse messages out of multibyte ring buffer. refactored wifi serialization libraries
2016-05-05 more errors taken out, got to a problem with message parsing on tcp rx and stopped to look at other message formats.
2016-05-08 implemented updated message format with checksumming.
2016-05-08 Commands are working on ESP with new message format. TCP is crashing upon successful transmission.
2016-05-11 Reconfigured bo otloader linker file to properly allocate heap space, improving stability of bootloader.
    reused a pointer in the ESP tcp receive method to reduce memory usage.
    fixed buffer overrun in address deserialization
    removed padding from message serialization
    added null checking in multibyte ring buffer.
    updated serial rx on esp to behave like wifi.c driver
    updated system monitor to make sure that its previous runtime is always
2016-05-14 Successfully downloaded and verified bootloader. Was writing wrong size to wrong address.
    Also increased the timeout on the http messages and am only sending one
    per iteration through the loop so we don't get multiple messages back
    for the same byte index.
2016-05-15 interactive assembly checkpoint
    working:
    press button on module a to set as input. hold button to change to
    output. module b gets messages telling it to configure itself as the
    opposite of module a. module b stores module a's address and sends back
    an accept message. module a stores module b's address. when module a
    times out, it sends a message to module b to cancel.
2016-05-16 Can now change channel direction from either module once the channel has been established.
2016-05-16 added comment blocks with some notes for Mike
2016-05-18 Fixed crash on ESP startup. sped up start by eliminating IMU init (for now) and moving the TCP init up in the order.
    Moving TCP init seems to have helped the speed with which the ESP finds
    a connection too, as we are no longer sending it a bunch of messages
    while it's trying to connect. With this firmware, you can reliably start
    linking channels with button presses about 10 seconds after powering on
    the board.
2016-05-19 updated ESP firmware to support 512 byte message length.
2016-05-21 Added messages for blinking and resetting the modules.
2016-05-22 commented out announce message parsing for now.
2016-05-28 Added length checking on message length and checksum fields, and verified that the values in those fields are numeric.
2016-05-31 Updated application code to work with new ESP firmware. Added application check for updates.
2016-06-01 Added hard fault handler, which led me to problems with message creation and/or queue. a message->previous is being set to 0x36000000+
    this causes a hard fault because the memory ends at 2002fff0.
